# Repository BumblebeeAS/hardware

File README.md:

This repo contains Bumblebee's old firmware for the Electrical subteam. Most of the code is from before 2023 so please proceed with caution.

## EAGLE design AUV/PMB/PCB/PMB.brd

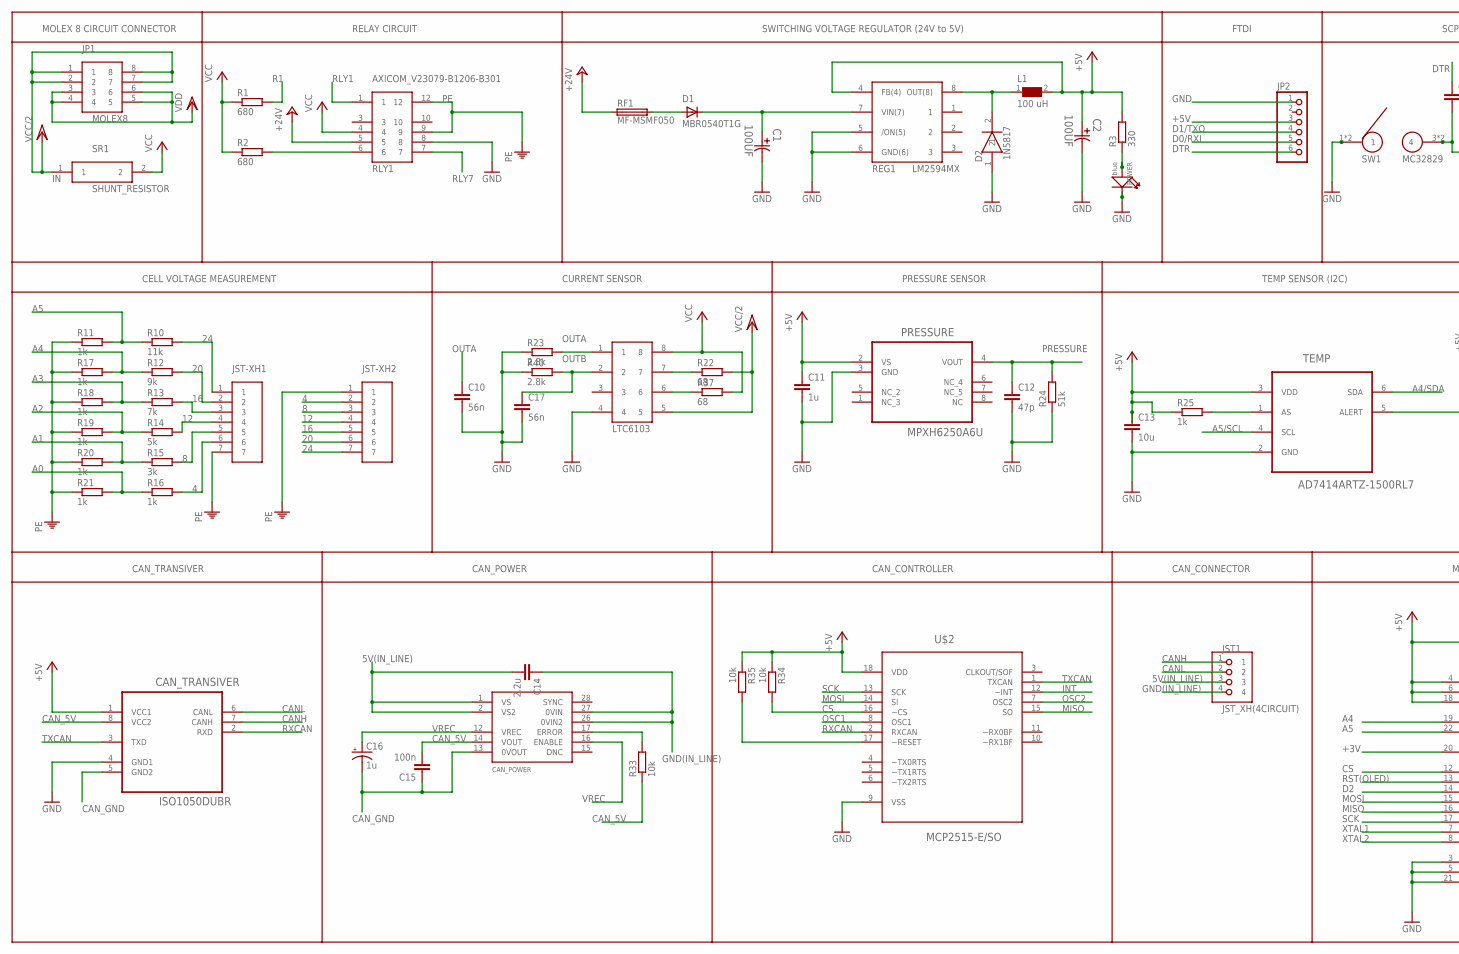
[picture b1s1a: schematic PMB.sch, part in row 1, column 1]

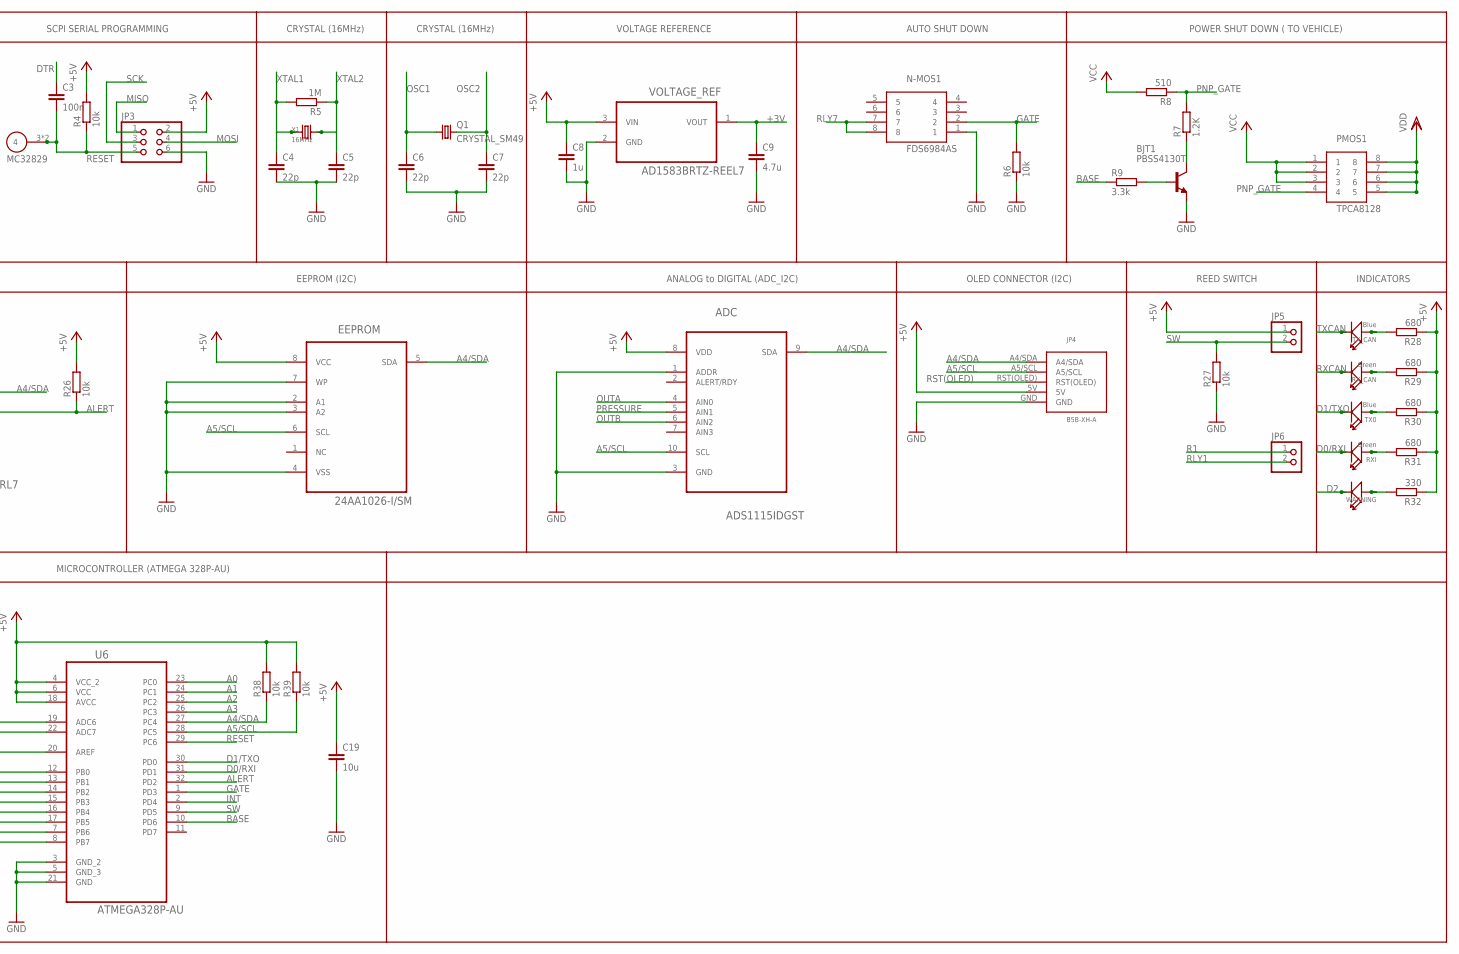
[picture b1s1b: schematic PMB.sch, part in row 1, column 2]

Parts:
ADC: ADS1115IDGST; SOP50P490X110-10N
BJT1: PBSS4130T; SOT-23
C1, C2: 100UF; CAPAE660X800N
C3, C15: 100n; 0805
C4, C5, C6, C7: 22p; 0805
C8, C11: 1u; 0805
C9: 4.7u; 0805
C10, C17: 56n; 0805
C12: 47p; 0805
C13, C19: 10u; 0805
C14: 2.2u; 0603-CAP
C16: 1u; EIA6032
CAN_POWER: DCR01SO; DCR01-SOIC28
CAN_TRANSIVER: ISO1050DUBR; SOIC254P1040X485-8N
D1: MBR0540T1G
D2: 1N5817
EEPROM: 24AA1026-I/SM; SOIC127P794X200-8N
JP1: MOLEX8; 026013144
JP2: PINHD-1X6/90; 1X06/90
JP3: PINHD-2X3; 2X03
JP4: B5B-XH-A
JP5, JP6: PINHD-1X2/90; 1X02/90
JST1: JST_XH(4CIRCUIT); JXT-XHP-4
JST-XH1, JST-XH2: JST_XH_1X7_2.5MM; SIL_1X8_2.5MM
L1: 100 uH; WE-PD_1030/1050
LTC1: LTC6103
N-MOS1: FDS6984AS; SO-8
PMOS1: TPCA8128
POWER: blue; LED-0805
PRESSURE: MPXH6250A6U; FREESCALE_CASE_1317
Q1: CRYSTAL_SM49; SM49
R1, R2, R28, R29, R30, R31: 680; R0805W
R3, R32: 330; R0805W
R4, R6, R26, R27, R33, R34, R35, R38, R39: 10k; R0805W
R5: 1M; R0805W
R7: 1.2K; R0805W
R8: 510; R0805W
R9: 3.3k; R0805W
R10: 11k; R0805W
R11, R16, R17, R18, R19, R20, R21, R25: 1k; R0805W
R12: 9k; R0805W
R13: 7k; R0805W
R14: 5k; R0805W
R15: 3k; R0805W
R22, R37: 68; R0805W
R23, R40: 2.8k; R0805W
R24: 51k; R0805W
REG1: LM2594MX
RF1: MF-MSMF050; MF-MSF050
RLY1: AXICOM_V23079-B1206-B301; RELAY_V23079_B1206
RXI: Green; LED-0805
RX_CAN: Green; LED-0805
SR1: SHUNT_RESISTOR; OARSXPR002FLF
SW1: MC32829
TEMP: AD7414ARTZ-1500RL7; SOT95P280X145-6N
TX0: Blue; LED-0805
TX_CAN: Blue; LED-0805
U6: ATMEGA328P-AU; QFP80P900X900X120-32N
U$2: MCP2515-E/SO; SOIC127P1030X265-18N
VOLTAGE_REF: AD1583BRTZ-REEL7; SOT95P237X112-3N
WARNING: LED-0805
X1: 16MHz; HC49US

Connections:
4: JST-XH1.6, JST-XH2.2, R16.2
5V(IN_LINE): C14.2, CAN_POWER.1 (VS), CAN_POWER.2 (VS2), JST1.3
8: JST-XH1.5, JST-XH2.3, R15.2
12: JST-XH1.4, JST-XH2.4, R14.2
16: JST-XH1.3, JST-XH2.5, R13.2
20: JST-XH1.2, JST-XH2.6, R12.2
24: JST-XH1.1, JST-XH2.7, R10.2
+3V: C9.1, U6.20 (AREF), VOLTAGE_REF.1 (VOUT)
+5V: ADC.8 (VDD), C2.1, C8.1, C11.1, C13.1, C19.1, CAN_TRANSIVER.1 (VCC1), EEPROM.8 (VCC), JP2.3, JP3.2, JP4.5V, JP5.1, L1.2, PRESSURE.2 (VS), R3.2, R4.2, R25.1, R26.2, R28.1, R29.1, R30.1, R31.1, R32.1, R34.1, R35.1, R38.2, R39.2, REG1.4 (FB(4)), TEMP.3 (VDD), U6.4 (VCC_2), U6.6 (VCC), U6.18 (AVCC), U$2.18 (VDD), VOLTAGE_REF.3 (VIN)
+24V: RF1.1, RLY1.5
A0: R16.1, R21.2, U6.23 (PC0)
A1: R15.1, R20.2, U6.24 (PC1)
A2: R14.1, R19.2, U6.25 (PC2)
A3: R13.1, R18.2, U6.26 (PC3)
A4: R12.1, R17.2, U6.19 (ADC6)
A4/SDA: ADC.9 (SDA), EEPROM.5 (SDA), JP4.A4/SDA, R38.1, TEMP.6 (SDA), U6.27 (PC4)
A5: R10.1, R11.2, U6.22 (ADC7)
A5/SCL: ADC.10 (SCL), EEPROM.6 (SCL), JP4.A5/SCL, R39.1, TEMP.4 (SCL), U6.28 (PC5)
ALERT: R26.1, TEMP.5 (ALERT), U6.32 (PD2)
BASE: R9.1, U6.10 (PD6)
CANH: CAN_TRANSIVER.7 (CANH), JST1.1
CANL: CAN_TRANSIVER.6 (CANL), JST1.2
CAN_5V: C15.2, CAN_POWER.14 (VOUT), CAN_TRANSIVER.8 (VCC2), R33.1
CAN_GND: C15.1, C16.P$2 (-), CAN_POWER.13 (0VOUT), CAN_TRANSIVER.5 (GND2)
CS: R34.2, U6.12 (PB0), U$2.16 (~CS)
D0/RXI: JP2.5, RXI.-, U6.31 (PD1)
D1/TXO: JP2.4, TX0.-, U6.30 (PD0)
D2: U6.14 (PB2), WARNING.-
DTR: C3.1, JP2.6
GATE: N-MOS1.2, R6.2, U6.1 (PD3)
GND: ADC.1 (ADDR), ADC.3 (GND), BJT1.E, C1.2, C2.2, C4.2, C5.2, C6.2, C7.2, C8.2, C9.2, C10.2, C11.2, C12.2, C13.2, C17.2, C19.2, CAN_TRANSIVER.4 (GND1), D2.1, EEPROM.2 (A1), EEPROM.3 (A2), EEPROM.4 (VSS), EEPROM.7 (WP), JP2.1, JP3.6, JP4.GND, LTC1.4, N-MOS1.1, POWER.-, PRESSURE.3 (GND), R6.1, R23.1, R24.1, R27.1, R40.1, REG1.5 (/ON(5)), REG1.6 (GND(6)), RLY1.8, SW1.1, SW1.2 (1), TEMP.2 (GND), U6.3 (GND_2), U6.5 (GND_3), U6.21 (GND), U$2.9 (VSS), VOLTAGE_REF.2 (GND)
GND(IN_LINE): C14.1, CAN_POWER.26 (0VIN2), CAN_POWER.27 (0VIN), JST1.4
INT: U6.2 (PD4), U$2.12 (~INT)
MISO: JP3.1, U6.16 (PB4), U$2.15 (SO)
MOSI: JP3.4, U6.15 (PB3), U$2.14 (SI)
unnamed: BJT1.B, R9.2
unnamed: D1.2, RF1.2
unnamed: C1.1, D1.1, REG1.7 (VIN(7))
unnamed: R2.2, RLY1.6
unnamed: D2.2, L1.1, REG1.8 (OUT(8))
unnamed: BJT1.C, R7.1
unnamed: POWER.+, R3.1
unnamed: LTC1.7, R22.1
unnamed: R25.2, TEMP.1 (AS)
unnamed: R32.2, WARNING.+
unnamed: R31.2, RXI.+
unnamed: R30.2, TX0.+
unnamed: R29.2, RX_CAN.+
unnamed: R28.2, TX_CAN.+
unnamed: LTC1.6, R37.1
unnamed: CAN_POWER.17 (ERROR), R33.2
unnamed: R35.2, U$2.17 (~RESET)
OSC1: C6.1, Q1.1, U$2.8 (OSC1)
OSC2: C7.1, Q1.2, U$2.7 (OSC2)
OUTA: ADC.4 (AIN0), C10.1, LTC1.1, R23.2
OUTB: ADC.6 (AIN2), C17.1, LTC1.2, R40.2
PE: JST-XH1.7, JST-XH2.1, R11.1, R17.1, R18.1, R19.1, R20.1, R21.1, RLY1.9, RLY1.12
PNP_GATE: PMOS1.4, R7.2, R8.1
PRESSURE: ADC.5 (AIN1), C12.1, PRESSURE.4 (VOUT), R24.2
R1: JP6.1, R1.2
RESET: C3.2, JP3.5, R4.1, SW1.3 (4), SW1.4, U6.29 (PC6)
RLY1: JP6.2, RLY1.1
RLY7: N-MOS1.7, N-MOS1.8, RLY1.7
RST(OLED): JP4.RST(OLED), U6.13 (PB1)
RXCAN: CAN_TRANSIVER.2 (RXD), RX_CAN.-, U$2.2 (RXCAN)
SCK: JP3.3, U6.17 (PB5), U$2.13 (SCK)
SW: JP5.2, R27.2, U6.9 (PD5)
TXCAN: CAN_TRANSIVER.3 (TXD), TX_CAN.-, U$2.1 (TXCAN)
VCC: LTC1.8, PMOS1.1, PMOS1.2, PMOS1.3, R1.1, R2.1, R8.2, R37.2, RLY1.4, SR1.2
VCC/2: JP1.1, JP1.2, JP1.7, JP1.8, LTC1.5, R22.2, SR1.1
VDD: JP1.3, JP1.4, JP1.5, JP1.6, PMOS1.5, PMOS1.6, PMOS1.7, PMOS1.8
VREC: C16.P$1 (+), CAN_POWER.12 (VREC), CAN_POWER.16 (ENABLE)
XTAL1: C4.1, R5.2, U6.7 (PB6), X1.1
XTAL2: C5.1, R5.1, U6.8 (PB7), X1.2

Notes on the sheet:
MOLEX 8 CIRCUIT CONNECTOR
RELAY CIRCUIT
SWITCHING VOLTAGE REGULATOR (24V to 5V)
FTDI
SCPI SERIAL PROGRAMMING
CRYSTAL (16MHz)
VOLTAGE REFERENCE
AUTO SHUT DOWN
POWER SHUT DOWN ( TO VEHICLE)
INDICATORS
REED SWITCH
OLED CONNECTOR (I2C)
ANALOG to DIGITAL (ADC_I2C)
EEPROM (I2C)
TEMP SENSOR (I2C)
PRESSURE SENSOR
CURRENT SENSOR
CELL VOLTAGE MEASUREMENT
CAN_TRANSIVER
CAN_POWER
CAN_CONTROLLER
CAN_CONNECTOR
MICROCONTROLLER (ATMEGA 328P-AU)

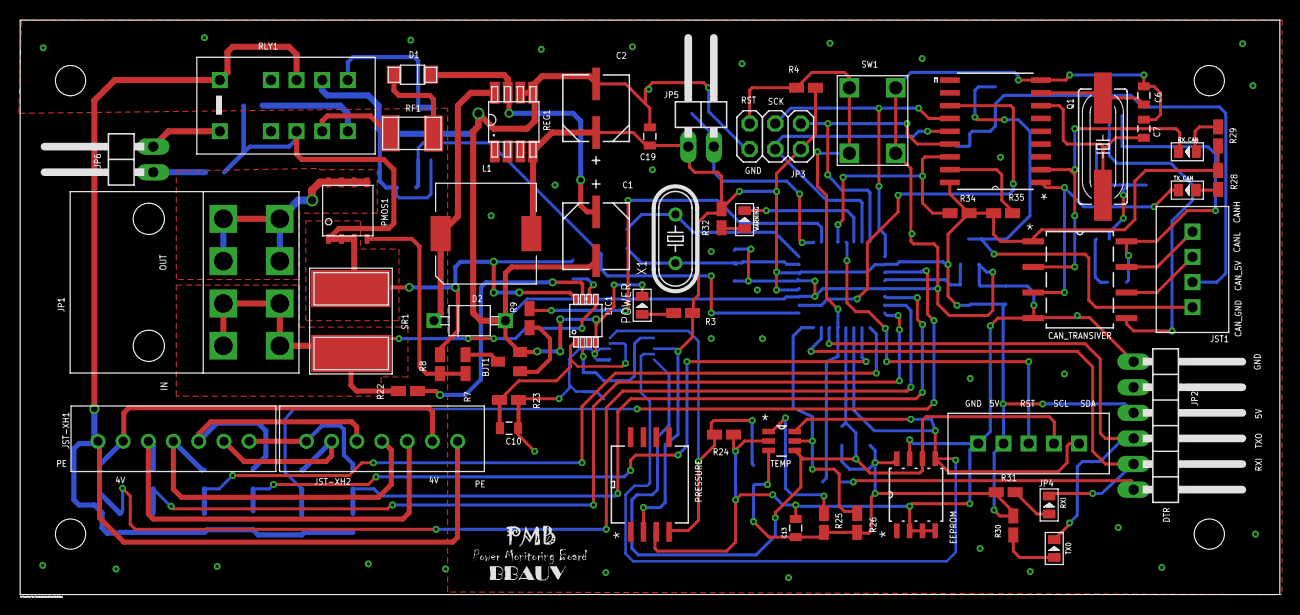
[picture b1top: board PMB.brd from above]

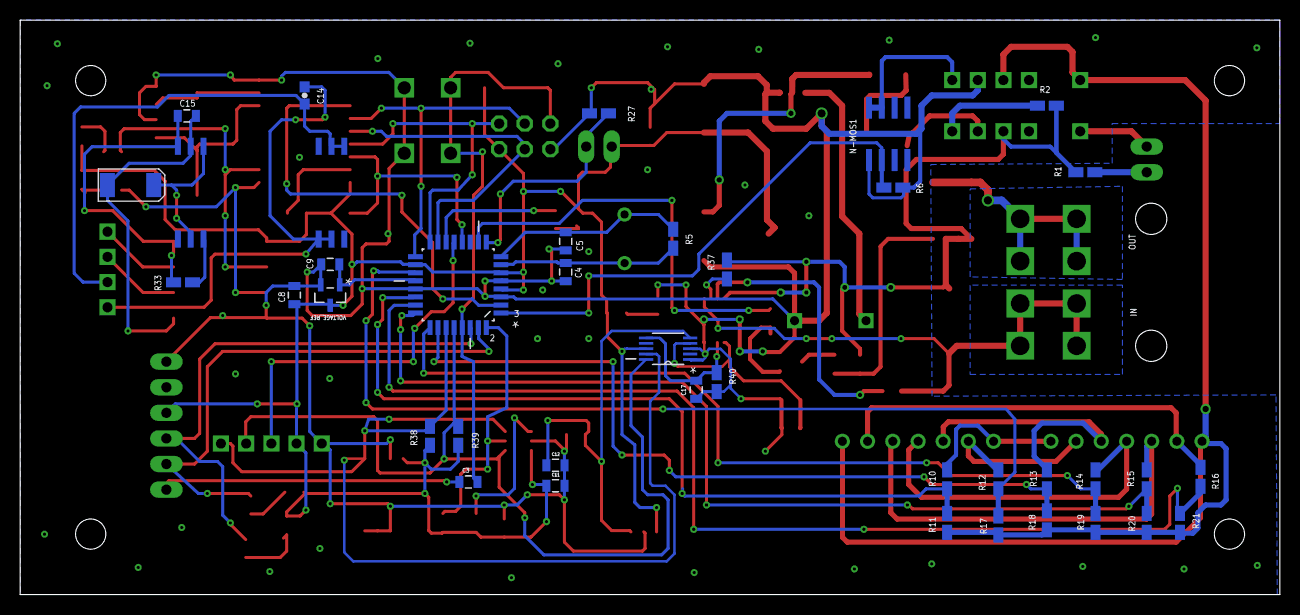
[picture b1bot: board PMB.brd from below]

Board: 2 copper layers, 125.0 x 57.0 mm, 95 parts (38 on the bottom side), 74 nets.

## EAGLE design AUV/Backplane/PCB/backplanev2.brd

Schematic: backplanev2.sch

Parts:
12VFAN: JP1E; JP1
24AA1026: 24AA1026-I/SM; SOIC127P794X200-8N
AD7414-1: AD7414-1; SOT23-6
ADUM1, ADUM2, ADUM3, ADUM4, ADUM1402: ADUM1402; SOIC127P1032X265-16N
C1, C2: 1uF; 1206
C3, C6, C7, C9, C12, C13, C24, C29, C32, C33, C35, C38, C39, C45, C51, C58, C59: 0.1uF; 0805
C4, C5, C8, C10, C11, C14, C25, C30, C31, C34, C36, C37, C40, C41, C44, C46, C47, C48, C52, C57, C60: 10uF; 0805
C15, C16, C17, C18, C22, C23, C42, C43: 22pF; 0805
C19, C20, C21, C26, C27, C28: 100nF; 0805
C53, C54: CAP_POL6032; EIA6032
C55, C56: CAP0603-CAP; 0603-CAP
D1, D3: 10V Zener; SOD-123
D2, D4: DIODESOD-123; SOD-123
FERRITE, FERRITE1, FERRITE2, FERRITE3, FERRITE4, FERRITE5, FERRITE6: FERRITE-74279201; RESC2013X65N
I2C: MA04-1
ISP: AVRISP-6; AVRISP
ISP-BP: AVRISP-6; AVRISP
JP5, JP6, JP8, JP9, JP10: JP2E; JP2
KILL-SWITCH: JP1E; JP1
LED1, LED2, LED3, LED4: LEDSMT1206; 1206
LED5: 5V logic power; 1206
LED-STRIP1, LED-STRIP2: LED STRIP; 1X04_LOCK
LTC4416: LTC4416; MSOP10
MCP2515-I/SO: MCP2515-I/SO; SOIC127P1034X264-18N
P-MOS, P-MOS1, P-MOS2, P-MOS3, P-MOS4, P-MOS5, P-MOS6: P-MOS; SOIC8
Q1, Q2, Q6: MMBT2222A; SOT23-3
Q3, Q4, Q5, Q7: 16Mhz; SM49
R1, R2: 10k; M0805
R3, R4, R7, R8, R33, R34, R35, R36, R39, R40, R41, R42, R51, R52, R53, R54, R57, R58, R59, R60, R61, R62, R63, R64, R65, R66, R67, R69, R70, R71, R75, R76, R77, R78, R93, R94, R95: 300; 0805
R5, R6, R9: 1M; 0805
R10, R11, R12, R13, R14, R15, R16, R17, R18, R31, R32, R37, R38, R44, R45, R49, R50, R55, R56, R68, R72, R74, R79, R101, R102, R103: RESISTOR0805-RES; 0805
R19, R20, R21, R22, R23, R24, R25, R26, R81, R82, R83, R84, R85, R86, R87, R88, R89, R90, R91, R92: R-EU_M0805; M0805
R27, R29, R43, R46, R47, R48, R73: 10k; 0805
R28, R30, R80: 1k; 0805
R104, R105: 120; 0805
RX: LEDCHIPLED_0805; CHIPLED_0805
RX-BP: LEDCHIPLED_0805; CHIPLED_0805
RX-CAN: LEDCHIPLED_0805; CHIPLED_0805
RX-PMB1, RX-PMB2: LEDCHIPLED_0805; CHIPLED_0805
RX-SA: LEDCHIPLED_0805; CHIPLED_0805
RX-TE: LEDCHIPLED_0805; CHIPLED_0805
RX-TH: LEDCHIPLED_0805; CHIPLED_0805
RXCAN: LEDCHIPLED_0805; CHIPLED_0805
SA: LEDCHIPLED_0805; CHIPLED_0805
SPARE: SA SPARE; 2X05
SPARE2: SA SPARE; 1X02
SW1, SW2: RESET; MC32829
SW_5V_BP, SW_5V_CAN, SW_5V_SA, SW_5V_TE, SW_5V_TH: LEDCHIPLED_0805; CHIPLED_0805
SW_USB_BP: LEDCHIPLED_0805; CHIPLED_0805
SW_USB_CAN: LEDCHIPLED_0805; CHIPLED_0805
SW_USB_PMB1, SW_USB_PMB2: LEDCHIPLED_0805; CHIPLED_0805
SW_USB_SA, SW_USB_SA1: LEDCHIPLED_0805; CHIPLED_0805
SW_USB_TE: LEDCHIPLED_0805; CHIPLED_0805
TE: LEDCHIPLED_0805; CHIPLED_0805
TH: LEDCHIPLED_0805; CHIPLED_0805
TX: LEDCHIPLED_0805; CHIPLED_0805
TX-BP: LEDCHIPLED_0805; CHIPLED_0805
TX-CAN: LEDCHIPLED_0805; CHIPLED_0805
TX-PMB1, TX-PMB2: LEDCHIPLED_0805; CHIPLED_0805
TX-SA: LEDCHIPLED_0805; CHIPLED_0805
TX-TE: LEDCHIPLED_0805; CHIPLED_0805
TX-TH: LEDCHIPLED_0805; CHIPLED_0805
TXCAN: LEDCHIPLED_0805; CHIPLED_0805
U1: ATMEGA328P_TQFP; TQFP32-08
U2, U3, U6, U7, U8, U9, U11: FT232RLSSOP; SSOP28DB
U4, U5: DCR010505U; SOIC127P1032X265-12NA
U13: ATMEGA2560-16AU; QFP50P1600X1600X120-100N
U$1: TERM-BLOCK-4POS
U$2, U$50, U$70: PLATED-HOLE
U$3, U$26, U$27: RJ45-DUAL-SOCKET; RJ45DOUBLESOCKET
U$4: MINIFIT-16CKT-STRAIGHTHEADER
U$5, U$22: 100UF; 100UF-AFK-CAP
U$6, U$12, U$55, U$56, U$60: LTC6103; MSOP8
U$7, U$32: IRLR3636PBF(N-MOS); TO252
U$8, U$9, U$10, U$17, U$19: S6B-XH-SM4-TB(LF)(SN)
U$11, U$16: FCN-365P040-BACKPLANE; FCN-365J040-BACKPLANE-JACK
U$13: MICROFIT-2CK-HEADER; MICROFIT-2CKT-HEADER
U$14: MICROFIT-8CKT-HEADER
U$15: MICROFIT-10CKT-HEADER
U$18, U$57: ADS1115; SOP50P490X110-10N
U$20, U$21, U$58, U$59, U$63: LVK25R002FER(CURRENT-SENSE-R)
U$23, U$24, U$28, U$31, U$33, U$44, U$46, U$48, U$49, U$51, U$53, U$54: MIC2005A-1YM5; SOT23-5
U$25: MCP2515-I/SO; SOIC127P1034X264-18N
U$29, U$30, U$41, U$47: USB-DUAL-SOCKET
U$34, U$40: ISO1050; DUB-8
U$35, U$36, U$37, U$38: MINIFIT-4CKT-2ROW-W2B-90DEG
U$39: MOLEX-MINIFIT-10CKT2ROW-90DEG-HEADER
U$45: MINIFIT-10CKT-STRAIGHTHEADER
U$52, U$61, U$64, U$65: MICROFIT-4CKT-HEADER
U$62: ADS1115DGST; SOP50P490X110-10N
U$76, U$78: N-MOS-SOIC8; SOIC8
U$77: N-MOS; SOIC8

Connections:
3.3V: U$11.B19, U$39.A5, U$39.B5
5V: 24AA1026.8 (VCC), AD7414-1.3 (VDD), C20.1, C21.1, C27.1, C28.1, C47.1, C55.1, C56.1, I2C.4, LED5.A, MCP2515-I/SO.18 (VDD), P-MOS1.1 (S), P-MOS1.2 (S), P-MOS1.3 (S), P-MOS5.1 (S), P-MOS5.2 (S), P-MOS5.3 (S), P-MOS6.1 (S), P-MOS6.2 (S), P-MOS6.3 (S), R17.2, R27.2, R29.2, R43.2, R46.2, R48.1, R72.1, R73.2, R79.2, R103.1, U1.4 (VCC), U1.6 (VCC), U4.1 (VS_2), U4.2 (VS), U5.1 (VS_2), U5.2 (VS), U13.10 (VCC_3), U13.31 (VCC_2), U13.61 (VCC_4), U13.80 (VCC), U13.100 (AVCC), U$1.P$3, U$5.POS (+), U$10.P$6, U$17.P$6, U$18.8 (VDD), U$19.P$6, U$22.POS (+), U$24.1 (VIN), U$24.3 (EN), U$25.18 (VDD), U$34.1 (VCC1), U$39.A3, U$39.B3, U$40.1 (VCC1), U$54.1 (VIN), U$54.3 (EN), U$57.8 (VDD), U$62.1 (ADDR), U$62.8 (VDD)
5VSA: P-MOS1.5 (D), P-MOS1.6 (D), P-MOS1.7 (D), P-MOS1.8 (D), R68.1, U$16.B19, U$46.1 (VIN), U$46.3 (EN)
5VTE: P-MOS6.5 (D), P-MOS6.6 (D), P-MOS6.7 (D), P-MOS6.8 (D), R66.1, U$11.B20, U$48.1 (VIN), U$48.3 (EN)
5VTH: P-MOS5.5 (D), P-MOS5.6 (D), P-MOS5.7 (D), P-MOS5.8 (D), R67.1, U$33.1 (VIN), U$33.3 (EN), U$45.L2
5V_ADC: R17.1, R18.2, U13.93 (PF4_(ADC4/TCK))
5V_CAN_BP: C19.2, C54.P$1 (+), R44.1, U5.14 (VO), U$40.8 (VCC2)
5V_UART_CAN: C26.2, C53.P$1 (+), R47.1, U4.14 (VO), U$34.8 (VCC2)
12IDSFI1: JP5.1, JP8.1, JP10.3, KILL-SWITCH.2, Q2.2 (E)
12V: 12VFAN.1, LED-STRIP1.1, LED-STRIP2.1, R15.2, U$1.P$2, U$13.PIN1, U$39.A2, U$39.B2
12V-TO-M4: U$39.A4, U$39.B4, U$64.BOT1 (B1), U$64.TOP1
12V_ADC: R15.1, R16.2, U13.92 (PF5_(ADC5/TMS))
24V1: LTC4416.8 (VS), P-MOS.1 (S), P-MOS.2 (S), P-MOS.3 (S), P-MOS3.1 (S), P-MOS3.2 (S), P-MOS3.3 (S), R101.2, U$20.I2
24V1_ADC: R101.1, R102.2, U13.94 (PF3_(ADC3))
24V2: U$20.I1, U$21.I2, U$52.BOT1 (B1), U$52.TOP1, U$61.BOT1 (B1), U$61.TOP1
24V2SA: U$14.BOT1 (B1), U$14.BOT2 (B2), U$14.BOT3 (B3), U$14.BOT4 (B4), U$15.T5, U$16.B20, U$21.I1
24V-ACOU: U$3.U4, U$3.U5, U$58.I1
24V-NAV: U$27.U4, U$27.U5, U$63.I1
24V-POE: U$1.P$4, U$58.I2, U$59.I2, U$63.I2, U$65.BOT1 (B1), U$65.TOP1
24V-SONAR: U$26.U4, U$26.U5, U$59.I1
A+: U$26.L1, U$26.U1
A-: U$26.L2, U$26.U2
ACOU-A+: U$3.L1, U$3.U1
ACOU-A-: U$3.L2, U$3.U2
ACOU-B+: U$3.L3, U$3.U3
ACOU-B-: U$3.L6, U$3.U6
ACOU_EN: U13.51 (PG0_(~WR)), U$77.4 (G)
ACOU_GND: U$3.U7, U$3.U8, U$77.5 (D), U$77.6 (D), U$77.7 (D), U$77.8 (D)
B1: LED-STRIP2.2, U$16.B16
B2: LED-STRIP1.2, U$16.A16
B+: U$26.L3, U$26.U3
B-: U$26.L6, U$26.U6
BATT1: LED1.A, LED2.C, LTC4416.9 (V1), P-MOS4.1 (S), P-MOS4.2 (S), P-MOS4.3 (S), R1.2, R6.2, R11.2, U$4.L5, U$4.L6, U$4.U5, U$4.U6, U$37.LL, U$37.LR, U$37.UL, U$37.UR
BATT1_ADC: R11.1, R12.2, U13.95 (PF2_(ADC2))
BATT2: LED3.A, LED4.C, LTC4416.7 (V2), P-MOS2.1 (S), P-MOS2.2 (S), P-MOS2.3 (S), R10.2, R13.2, U$4.L7, U$4.L8, U$4.U7, U$4.U8, U$38.LL, U$38.LR, U$38.UL, U$38.UR
BATT2_ADC: R13.1, R14.2, U13.96 (PF1_(ADC1))
CANH: R104.2, R105.2, U$10.P$4, U$11.A1, U$16.A1, U$17.P$4, U$19.P$4, U$34.7 (CANH), U$40.7 (CANH), U$45.L1
CANL: R104.1, R105.1, U$10.P$3, U$11.A2, U$16.A2, U$17.P$3, U$19.P$3, U$34.6 (CANL), U$40.6 (CANL), U$45.U1
CAN_RXD: RXCAN.A, U$25.2 (RXCAN), U$34.2 (RXD)
CAN_RXD_BP: MCP2515-I/SO.2 (RXCAN), RX.A, U$40.2 (RXD)
CAN_TXD_BP: MCP2515-I/SO.1 (TXCAN), TX.A, U$40.3 (TXD)
CTS_BP: ADUM1402.11 (VID)
CTS_CAN: ADUM1.11 (VID)
CTS_CAN_ISO: ADUM1.6 (VOD)
CTS_TH_ISO: ADUM2.6 (VOD)
D+_BP: U2.15 (USBDP), U$30.U3 (UDP)
D+_CAN: U6.15 (USBDP), U$41.U3 (UDP)
D+_PMB1: U9.15 (USBDP), U$29.L3 (LDP)
D+_PMB2: U11.15 (USBDP), U$29.U3 (UDP)
D+_SA: U7.15 (USBDP), U$47.L3 (LDP)
D+_TE: U8.15 (USBDP), U$47.U3 (UDP)
D+_TH: U3.15 (USBDP), U$30.L3 (LDP)
D-_BP: U2.16 (USBDM), U$30.U2 (UDM)
D-_CAN: U6.16 (USBDM), U$41.U2 (UDM)
D-_PMB1: U9.16 (USBDM), U$29.L2 (LDM)
D-_PMB2: U11.16 (USBDM), U$29.U2 (UDM)
D-_SA: U7.16 (USBDM), U$47.L2 (LDM)
D-_TE: U8.16 (USBDM), U$47.U2 (UDM)
D-_TH: U3.16 (USBDM), U$30.L2 (LDM)
DTR_BP: ADUM1402.13 (VOB), C44.1
DTR_BP_ISO: ADUM1402.4 (VIB), U2.2 (DTR)
DTR_CAN: ADUM1.13 (VOB), C41.1
DTR_CAN_ISO: ADUM1.4 (VIB), U6.2 (DTR)
DTR_PMB1_ISO: U9.2 (DTR), U$8.P$6
DTR_PMB2_ISO: U11.2 (DTR), U$9.P$6
DTR_SA: ADUM3.13 (VOB), U$16.B2
DTR_SA_ISO: ADUM3.4 (VIB), U7.2 (DTR)
DTR_TE: ADUM4.13 (VOB), U$11.B2
DTR_TE_ISO: ADUM4.4 (VIB), U8.2 (DTR)
DTR_TH: ADUM2.13 (VOB), U$45.L3
DTR_TH_ISO: ADUM2.4 (VIB), U3.2 (DTR)
G1: LED-STRIP2.3, U$16.B17
G2: LED-STRIP1.3, U$16.A17
GATE1: LTC4416.10 (G1), P-MOS3.4 (G), P-MOS4.4 (G)
GATE2: LTC4416.6 (G2), P-MOS.4 (G), P-MOS2.4 (G)
GND: 12VFAN.2, 24AA1026.2 (A1), 24AA1026.3 (A2), 24AA1026.4 (VSS), 24AA1026.7 (WP), AD7414-1.1 (AS), AD7414-1.2 (GND), ADUM1.9 (GND2_2), ADUM1.15 (GND2), ADUM2.9 (GND2_2), ADUM2.15 (GND2), ADUM3.9 (GND2_2), ADUM3.15 (GND2), ADUM4.9 (GND2_2), ADUM4.15 (GND2), ADUM1402.9 (GND2_2), ADUM1402.15 (GND2), C4.2, C6.2, C10.2, C12.2, C15.1, C16.1, C17.1, C18.1, C19.1, C20.2, C21.2, C22.1, C23.1, C25.2, C26.1, C27.2, C28.2, C30.2, C32.2, C36.2, C38.2, C42.1, C43.1, C47.2, C48.1, C55.2, C56.2, C58.2, I2C.1, ISP.6 (GND), ISP-BP.6 (GND), JP8.3, JP10.1, KILL-SWITCH.1, LTC4416.3 (GND), MCP2515-I/SO.9 (VSS), R2.1, R12.1, R14.1, R16.1, R18.1, R19.2, R20.2, R23.2, R24.2, R36.2, R42.2, R54.2, R60.2, R61.1, R62.1, R78.2, R81.2, R82.2, R85.2, R86.2, R89.2, R90.2, R93.1, R94.1, R95.1, R102.1, SA.C, SW1.P$1, SW1.P$4, SW2.P$1, SW2.P$4, TE.C, TH.C, U1.3 (GND), U1.21 (AGND), U4.13 (0VOUT), U4.26 (0VIN_2), U4.27 (0VIN), U5.13 (0VOUT), U5.26 (0VIN_2), U5.27 (0VIN), U13.11 (GND_2), U13.32 (GND_4), U13.62 (GND_3), U13.81 (GND_5), U13.99 (GND), U$1.P$1, U$2.P$1, U$4.L1, U$4.L2, U$4.L3, U$4.L4, U$4.U1, U$4.U2, U$4.U3, U$4.U4, U$5.NEG (-), U$6.4 (V-), U$7.3 (D), U$10.P$1, U$11.A19, U$11.A20, U$11.B1, U$12.4 (V-), U$14.TOP3, U$14.TOP4, U$16.A19, U$16.A20, U$16.B1, U$17.P$1, U$18.3 (GND), U$19.P$1, U$22.NEG (-), U$24.2 (GND), U$25.9 (VSS), U$32.3 (D), U$33.2 (GND), U$34.4 (GND1), U$34.5 (GND2), U$39.A1, U$39.B1, U$40.4 (GND1), U$40.5 (GND2), U$45.U2, U$46.2 (GND), U$48.2 (GND), U$52.BOT2 (B2), U$52.TOP2, U$54.2 (GND), U$55.4 (V-), U$56.4 (V-), U$57.3 (GND), U$60.4 (V-), U$61.BOT2 (B2), U$61.TOP2, U$62.3 (GND), U$64.BOT2 (B2), U$64.TOP2, U$65.BOT2 (B2), U$65.TOP2, U$70.P$1, U$76.1 (S), U$76.2 (S), U$76.3 (S), U$77.1 (S), U$77.2 (S), U$77.3 (S), U$78.1 (S), U$78.2 (S), U$78.3 (S)
GND_IN: C1.2, C2.2, D1.A, D3.A, R3.1, R4.1, R5.1, R7.1, R8.1, R9.1, U$7.2 (S), U$32.2 (S), U$35.LL, U$35.LR, U$35.UL, U$35.UR, U$36.LL, U$36.LR, U$36.UL, U$36.UR
INTERRUPT_UART_CAN: U$25.12 (~INT)
INT_BP: MCP2515-I/SO.12 (~INT)
L1: U$14.TOP1, U$16.B15
L2: U$14.TOP2, U$16.A15
LVE1: ADUM1402.7 (VE1), R32.1
LVE2: ADUM2.7 (VE1), R38.1
LVE3: ADUM3.7 (VE1), R50.1
LVE4: ADUM4.7 (VE1), R56.1
LVE7: ADUM1.7 (VE1), R74.1
M1: U$15.B5, U$16.B14
M2: U$15.B4, U$16.A14
M3: U$15.T4, U$16.B13
M4: U$15.B3, U$16.A13
M5: U$15.T3, U$16.B12
M6: U$15.B2, U$16.A12
M7: U$15.T2, U$16.B11
M8: U$15.B1, U$16.A11
M9: U$15.T1, U$16.B10
MISO_BP: ISP-BP.1 (MISO), MCP2515-I/SO.15 (SO), U13.22 ((MISO/PCINT3)_PB3)
MISO_UART_CAN: ISP.1 (MISO), U1.16 (PB4(MISO)), U$25.15 (SO)
MOSI_BP: ISP-BP.4 (MOSI), MCP2515-I/SO.14 (SI), U13.21 ((MOSI/PCINT2)_PB2)
MOSI_UART_CAN: ISP.4 (MOSI), U1.15 (PB3(MOSI/OC2)), U$25.14 (SI)
unnamed: P-MOS3.5 (D), P-MOS3.6 (D), P-MOS3.7 (D), P-MOS3.8 (D), P-MOS4.5 (D), P-MOS4.6 (D), P-MOS4.7 (D), P-MOS4.8 (D)
unnamed: P-MOS.5 (D), P-MOS.6 (D), P-MOS.7 (D), P-MOS.8 (D), P-MOS2.5 (D), P-MOS2.6 (D), P-MOS2.7 (D), P-MOS2.8 (D)
unnamed: R33.2, TX-BP.C
unnamed: R33.1, U2.23 (TXLED)
unnamed: R34.2, RX-BP.C
unnamed: FERRITE.2, U$23.1 (VIN), U$23.3 (EN)
unnamed: ADUM1402.10 (VE2), R31.1
unnamed: R35.2, SW_USB_BP.C
unnamed: R36.1, SW_5V_BP.A
unnamed: R39.2, RX-TH.C
unnamed: R34.1, U2.22 (RXLED)
unnamed: R40.2, TX-TH.C
unnamed: ADUM2.10 (VE2), R37.1
unnamed: FERRITE1.2, U$31.1 (VIN), U$31.3 (EN)
unnamed: R41.2, SW_USB_SA.C
unnamed: R39.1, U3.22 (RXLED)
unnamed: R40.1, U3.23 (TXLED)
unnamed: R42.1, SW_5V_TH.A
unnamed: C22.2, Q3.1, U$25.7 (OSC2)
unnamed: C23.2, Q3.2, U$25.8 (OSC1)
unnamed: C15.2, MCP2515-I/SO.7 (OSC2), Q4.1
unnamed: C16.2, MCP2515-I/SO.8 (OSC1), Q4.2
unnamed: R46.1, U$25.17 (~RESET)
unnamed: C42.2, Q7.1, U1.7 (PB6(XTAL1/TOSC1))
unnamed: MCP2515-I/SO.17 (~RESET), R43.1
unnamed: R47.2, U4.17 (~ERROR)
unnamed: R51.2, TX-SA.C
unnamed: R52.2, RX-SA.C
unnamed: ADUM3.10 (VE2), R49.1
unnamed: FERRITE2.2, U$44.1 (VIN), U$44.3 (EN)
unnamed: R53.2, SW_USB_SA1.C
unnamed: R51.1, U7.23 (TXLED)
unnamed: R52.1, U7.22 (RXLED)
unnamed: LED2.A, R3.2
unnamed: LED1.C, R4.2
unnamed: R54.1, SW_5V_SA.A
unnamed: R57.2, TX-TE.C
unnamed: R58.2, RX-TE.C
unnamed: ADUM4.10 (VE2), R55.1
unnamed: FERRITE3.2, U$28.1 (VIN), U$28.3 (EN)
unnamed: R59.2, SW_USB_TE.C
unnamed: R61.2, TXCAN.C
unnamed: R62.2, RXCAN.C
unnamed: R93.2, TX.C
unnamed: R63.2, TX-PMB1.C
unnamed: R64.2, RX-PMB1.C
unnamed: R66.2, TE.A
unnamed: FERRITE4.2, U$49.1 (VIN), U$49.3 (EN)
unnamed: R75.2, RX-CAN.C
unnamed: R76.2, TX-CAN.C
unnamed: R67.2, TH.A
unnamed: R57.1, U8.23 (TXLED)
unnamed: R58.1, U8.22 (RXLED)
unnamed: R60.1, SW_5V_TE.A
unnamed: JP5.2, P-MOS5.4 (G), R29.1
unnamed: JP5.3, Q2.3 (C)
unnamed: JP6.2, P-MOS1.4 (G), R27.1
unnamed: Q2.1 (B), R30.1
unnamed: JP6.3, Q1.3 (C)
unnamed: Q1.1 (B), R28.1
unnamed: JP6.1, JP8.2, Q1.2 (E)
unnamed: ADUM1.10 (VE2), R45.1
unnamed: R65.2, SW_USB_PMB1.C
unnamed: R63.1, U9.23 (TXLED)
unnamed: R64.1, U9.22 (RXLED)
unnamed: R68.2, SA.A
unnamed: R69.2, TX-PMB2.C
unnamed: R70.2, RX-PMB2.C
unnamed: R44.2, U5.17 (~ERROR)
unnamed: R75.1, U6.22 (RXLED)
unnamed: FERRITE5.2, U$51.1 (VIN), U$51.3 (EN)
unnamed: R71.2, SW_USB_PMB2.C
unnamed: R69.1, U11.23 (TXLED)
unnamed: R70.1, U11.22 (RXLED)
unnamed: R76.1, U6.23 (TXLED)
unnamed: R94.2, RX.C
unnamed: LED5.C, R95.2
unnamed: LTC4416.2 (E1), R1.1
unnamed: LTC4416.4 (!E2), R2.2
unnamed: C48.2, U13.98 (AREF)
unnamed: C43.2, Q7.2, U1.8 (PB7(XTAL2/TOSC2))
unnamed: C17.2, Q5.1, U13.33 (XTAL2)
unnamed: C18.2, Q5.2, U13.34 (XTAL1)
unnamed: FERRITE6.2, U$53.1 (VIN), U$53.3 (EN)
unnamed: R77.2, SW_USB_CAN.C
unnamed: R78.1, SW_5V_CAN.A
unnamed: Q6.1 (B), R80.1
unnamed: JP9.3, Q6.3 (C)
unnamed: JP9.2, P-MOS6.4 (G), R79.1
unnamed: JP9.1, JP10.2, Q6.2 (E)
unnamed: R83.1, U$55.5 (+INB), U$58.V1
unnamed: R84.1, U$55.8 (+INA), U$58.V2
unnamed: R81.1, U$55.1 (OUTA), U$57.4 (AIN0)
unnamed: R82.1, U$55.2 (OUTB), U$57.5 (AIN1)
unnamed: R83.2, U$55.7 (-INA)
unnamed: R84.2, U$55.6 (-INB)
unnamed: R87.1, U$56.5 (+INB), U$59.V1
unnamed: R88.1, U$56.8 (+INA), U$59.V2
unnamed: R85.1, U$56.1 (OUTA), U$57.7 (AIN3)
unnamed: R86.1, U$56.2 (OUTB), U$57.6 (AIN2)
unnamed: R87.2, U$56.7 (-INA)
unnamed: R88.2, U$56.6 (-INB)
unnamed: R91.1, U$60.5 (+INB), U$63.V1
unnamed: R92.1, U$60.8 (+INA), U$63.V2
unnamed: R89.1, U$60.1 (OUTA), U$62.4 (AIN0)
unnamed: R90.1, U$60.2 (OUTB), U$62.5 (AIN1)
unnamed: R91.2, U$60.7 (-INA)
unnamed: R92.2, U$60.6 (-INB)
unnamed: C1.1, D2.A, R5.2, R6.1, U$32.1 (G)
unnamed: LED4.A, R7.2
unnamed: D1.C, D2.C
unnamed: LED3.C, R8.2
unnamed: C2.1, D4.A, R9.2, R10.1, U$7.1 (G)
unnamed: D3.C, D4.C
unnamed: R21.1, U$6.5 (+INB), U$20.V1
unnamed: R22.1, U$6.8 (+INA), U$20.V2
unnamed: R19.1, U$6.1 (OUTA), U$18.7 (AIN3)
unnamed: R20.1, U$6.2 (OUTB), U$18.6 (AIN2)
unnamed: R21.2, U$6.7 (-INA)
unnamed: R22.2, U$6.6 (-INB)
unnamed: R25.1, U$12.5 (+INB), U$21.V1
unnamed: R26.1, U$12.8 (+INA), U$21.V2
unnamed: R23.1, U$12.1 (OUTA), U$18.4 (AIN0)
unnamed: R24.1, U$12.2 (OUTB), U$18.5 (AIN1)
unnamed: R25.2, U$12.7 (-INA)
unnamed: R26.2, U$12.6 (-INB)
NAV-A+: U$27.L1, U$27.U1
NAV-A-: U$27.L2, U$27.U2
NAV-B+: U$27.L3, U$27.U3
NAV-B-: U$27.L6, U$27.U6
NAV_EN: U13.53 (PC0_(A8)), U$76.4 (G)
NAV_GND: U$27.U7, U$27.U8, U$76.5 (D), U$76.6 (D), U$76.7 (D), U$76.8 (D)
PRES: U$13.PIN2, U$16.A10
R1: LED-STRIP2.4, U$16.B18
R2: LED-STRIP1.4, U$16.A18
RESET_BP: C44.2, ISP-BP.5 (RST), R103.2, SW2.P$2, SW2.P$3, U13.30 (~RESET)
RESET_UART_CAN: C41.2, ISP.5 (RST), R72.2, SW1.P$2, SW1.P$3, U1.29 (PC6(/RESET))
RX_BP: ADUM1402.14 (VOA), U13.2 ((RXD0/PCINT8)_PE0)
RX_BP_ISO: ADUM1402.3 (VIA), U2.1 (TXD)
RX_CAN: ADUM1.14 (VOA), TXCAN.A, U1.30 (PD0(RXD)), U$25.1 (TXCAN), U$34.3 (TXD)
RX_CAN_ISO: ADUM1.3 (VIA), U6.1 (TXD)
RX_PMB1_ISO: U9.1 (TXD), U$8.P$4
RX_PMB2_ISO: U11.1 (TXD), U$9.P$4
RX_SA: ADUM3.14 (VOA), U$16.B3
RX_SA_1: SPARE2.2, U$16.A3
RX_SA_ISO: ADUM3.3 (VIA), U7.1 (TXD)
RX_TE: ADUM4.14 (VOA), U$11.B3
RX_TE_ISO: ADUM4.3 (VIA), U8.1 (TXD)
RX_TH: ADUM2.14 (VOA), U$45.U4
RX_TH_ISO: ADUM2.3 (VIA), U3.1 (TXD)
SA_EN: R28.2, U13.50 ((T0)_PD7)
SCK_BP: ISP-BP.3 (SCK), MCP2515-I/SO.13 (SCK), U13.20 ((SCK/PCINT1)_PB1)
SCK_UART_CAN: ISP.3 (SCK), U1.17 (PB5(SCK)), U$25.13 (SCK)
SCL: 24AA1026.6 (SCL), AD7414-1.4 (SCL), I2C.2, U13.43 ((SCL/INT0)_PD0), U$18.1 (ADDR), U$18.10 (SCL), U$57.10 (SCL), U$62.10 (SCL)
SDA: 24AA1026.5 (SDA), AD7414-1.6 (SDA), I2C.3, U13.44 ((SDA/INT1)_PD1), U$18.9 (SDA), U$57.1 (ADDR), U$57.9 (SDA), U$62.9 (SDA)
SONAR_EN: U13.52 (PG1_(~RD)), U$78.4 (G)
SONAR_GND: U$26.U7, U$26.U8, U$78.5 (D), U$78.6 (D), U$78.7 (D), U$78.8 (D)
SPARE1: SPARE.2, U$16.B9
SPARE2: SPARE.4, U$16.B8
SPARE3: SPARE.6, U$16.B7
SPARE4: SPARE.8, U$16.B6
SPARE5: SPARE.10, U$16.B5
SPARE6: SPARE.1, U$16.A9
SPARE7: SPARE.3, U$16.A8
SPARE8: SPARE.5, U$16.A7
SPARE9: SPARE.7, U$16.A6
SPARE10: SPARE.9, U$16.A5
SPARE_TH_1: U$45.U3
SPARE_TH_2: U$45.U5
SPARE_TH_3: U$45.L5
SS_BP: MCP2515-I/SO.16 (~CS), R73.1, U13.17 ((OC4C)_PH5)
SS_UART_CAN: R48.2, U1.12 (PB0(ICP)), U$25.16 (~CS)
SW_5V_BP: ADUM1402.16 (VDD2), C4.1, C6.1, R31.2, SW_5V_BP.C, U$24.5 (VOUT)
SW_5V_CAN: ADUM1.16 (VDD2), C25.1, C58.1, R45.2, SW_5V_CAN.C, U$54.5 (VOUT)
SW_5V_SA: ADUM3.16 (VDD2), C30.1, C32.1, R49.2, SW_5V_SA.C, U$46.5 (VOUT)
SW_5V_TE: ADUM4.16 (VDD2), C36.1, C38.1, R55.2, SW_5V_TE.C, U$48.5 (VOUT)
SW_5V_TH: ADUM2.16 (VDD2), C10.1, C12.1, R37.2, SW_5V_TH.C, U$33.5 (VOUT)
SW_USB+_BP: ADUM1402.1 (VDD1), C3.1, C5.1, C7.1, C8.1, R32.2, R35.1, RX-BP.A, TX-BP.A, U2.4 (VCCIO), U2.20 (VCC), U$23.5 (VOUT)
SW_USB+_CAN: ADUM1.1 (VDD1), C24.1, C57.1, C59.1, C60.1, R74.2, R77.1, RX-CAN.A, TX-CAN.A, U6.4 (VCCIO), U6.20 (VCC), U$53.5 (VOUT)
SW_USB+_PMB1: C45.1, C46.1, R65.1, RX-PMB1.A, TX-PMB1.A, U9.4 (VCCIO), U9.20 (VCC), U$8.P$3, U$49.5 (VOUT)
SW_USB+_PMB2: C51.1, C52.1, R71.1, RX-PMB2.A, TX-PMB2.A, U11.4 (VCCIO), U11.20 (VCC), U$9.P$3, U$51.5 (VOUT)
SW_USB+_SA: ADUM3.1 (VDD1), C29.1, C31.1, C33.1, C34.1, R50.2, R53.1, RX-SA.A, TX-SA.A, U7.4 (VCCIO), U7.20 (VCC), U$44.5 (VOUT)
SW_USB+_TE: ADUM4.1 (VDD1), C35.1, C37.1, C39.1, C40.1, R56.2, R59.1, RX-TE.A, TX-TE.A, U8.4 (VCCIO), U8.20 (VCC), U$28.5 (VOUT)
SW_USB+_TH: ADUM2.1 (VDD1), C9.1, C11.1, C13.1, C14.1, R38.2, R41.1, RX-TH.A, TX-TH.A, U3.4 (VCCIO), U3.20 (VCC), U$31.5 (VOUT)
TE_EN: R80.2, U13.49 ((T1)_PD6)
TH_EN: R30.2, U13.97 (PF0_(ADC0))
TX_BP: ADUM1402.12 (VIC), U13.3 ((TXD0)_PE1)
TX_BP_ISO: ADUM1402.5 (VOC), U2.5 (RXD)
TX_CAN: ADUM1.12 (VIC), U1.31 (PD1(TXD))
TX_CAN_ISO: ADUM1.5 (VOC), U6.5 (RXD)
TX_PMB1_ISO: U9.5 (RXD), U$8.P$5
TX_PMB2_ISO: U11.5 (RXD), U$9.P$5
TX_SA: ADUM3.12 (VIC), U$16.B4
TX_SA_1: SPARE2.1, U$16.A4
TX_SA_ISO: ADUM3.5 (VOC), U7.5 (RXD)
TX_TE: ADUM4.12 (VIC), U$11.B4
TX_TE_ISO: ADUM4.5 (VOC), U8.5 (RXD)
TX_TH: ADUM2.12 (VIC), U$45.L4
TX_TH_ISO: ADUM2.5 (VOC), U3.5 (RXD)
USB+_BP: FERRITE.1, U$30.U1 (UVCC)
USB+_CAN: FERRITE6.1, U$41.U1 (UVCC)
USB+_PMB1: FERRITE4.1, U$29.L1 (LVCC)
USB+_PMB2: FERRITE5.1, U$29.U1 (UVCC)
USB+_SA: FERRITE2.1, U$47.L1 (LVCC)
USB+_TE: FERRITE3.1, U$47.U1 (UVCC)
USB+_TH: FERRITE1.1, U$30.L1 (LVCC)
USB-_BP: ADUM1402.2 (GND1_2), ADUM1402.8 (GND1), C3.2, C5.2, C7.2, C8.2, SW_USB_BP.A, U2.7 (GND7), U2.18 (GND18), U2.21 (GND21), U2.25 (AGND), U2.26 (TEST), U$23.2 (GND), U$30.CHA3, U$30.CHA4, U$30.U4 (UGND)
USB-_CAN: ADUM1.2 (GND1_2), ADUM1.8 (GND1), C24.2, C57.2, C59.2, C60.2, SW_USB_CAN.A, U6.7 (GND7), U6.18 (GND18), U6.21 (GND21), U6.25 (AGND), U6.26 (TEST), U$41.CHA1, U$41.CHA2, U$41.CHA3, U$41.CHA4, U$41.U4 (UGND), U$53.2 (GND)
USB-_PMB1: C45.2, C46.2, SW_USB_PMB1.A, U9.7 (GND7), U9.18 (GND18), U9.21 (GND21), U9.25 (AGND), U9.26 (TEST), U$8.P$1, U$29.CHA1, U$29.CHA2, U$29.L4 (LGND), U$49.2 (GND)
USB-_PMB2: C51.2, C52.2, SW_USB_PMB2.A, U11.7 (GND7), U11.18 (GND18), U11.21 (GND21), U11.25 (AGND), U11.26 (TEST), U$9.P$1, U$29.CHA3, U$29.CHA4, U$29.U4 (UGND), U$51.2 (GND)
USB-_SA: ADUM3.2 (GND1_2), ADUM3.8 (GND1), C29.2, C31.2, C33.2, C34.2, SW_USB_SA1.A, U7.7 (GND7), U7.18 (GND18), U7.21 (GND21), U7.25 (AGND), U7.26 (TEST), U$44.2 (GND), U$47.CHA1, U$47.CHA2, U$47.L4 (LGND)
USB-_TE: ADUM4.2 (GND1_2), ADUM4.8 (GND1), C35.2, C37.2, C39.2, C40.2, SW_USB_TE.A, U8.7 (GND7), U8.18 (GND18), U8.21 (GND21), U8.25 (AGND), U8.26 (TEST), U$28.2 (GND), U$47.CHA3, U$47.CHA4, U$47.U4 (UGND)
USB-_TH: ADUM2.2 (GND1_2), ADUM2.8 (GND1), C9.2, C11.2, C13.2, C14.2, SW_USB_SA.A, U3.7 (GND7), U3.18 (GND18), U3.21 (GND21), U3.25 (AGND), U3.26 (TEST), U$30.CHA1, U$30.CHA2, U$30.L4 (LGND), U$31.2 (GND)
VREC: C54.P$2 (-), U5.12 (VREC), U5.16 (EN)
VREC2: C53.P$2 (-), U4.12 (VREC), U4.16 (EN)

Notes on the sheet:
telemetry board
thruster board
S&A board
to ethernet switch
to sonar
to nav housing
to acoustic
to kill switch
Soft-start
Daughter boards power control
Load balancer
Power connectors
backplane MCU
Isolated USB-UART converters
USB-UART converters
CAN-USB converter
Power over Ethernet injectors
CAN connectors
Current measurements
Voltage measurements
POEs power control
12V fan power
CAN-USB CONVERTER
VOLTAGE MEASUREMENT
CAN CONNECTORS
CURRENT MEASUREMENT
POE
LOAD BALANCER
SOFT START
POWER CONN
BACKPLANE MCU
USB-UART CONVERTER
ISOLATED USB-UART CONVERTER
Temperature sensor
EEPROM

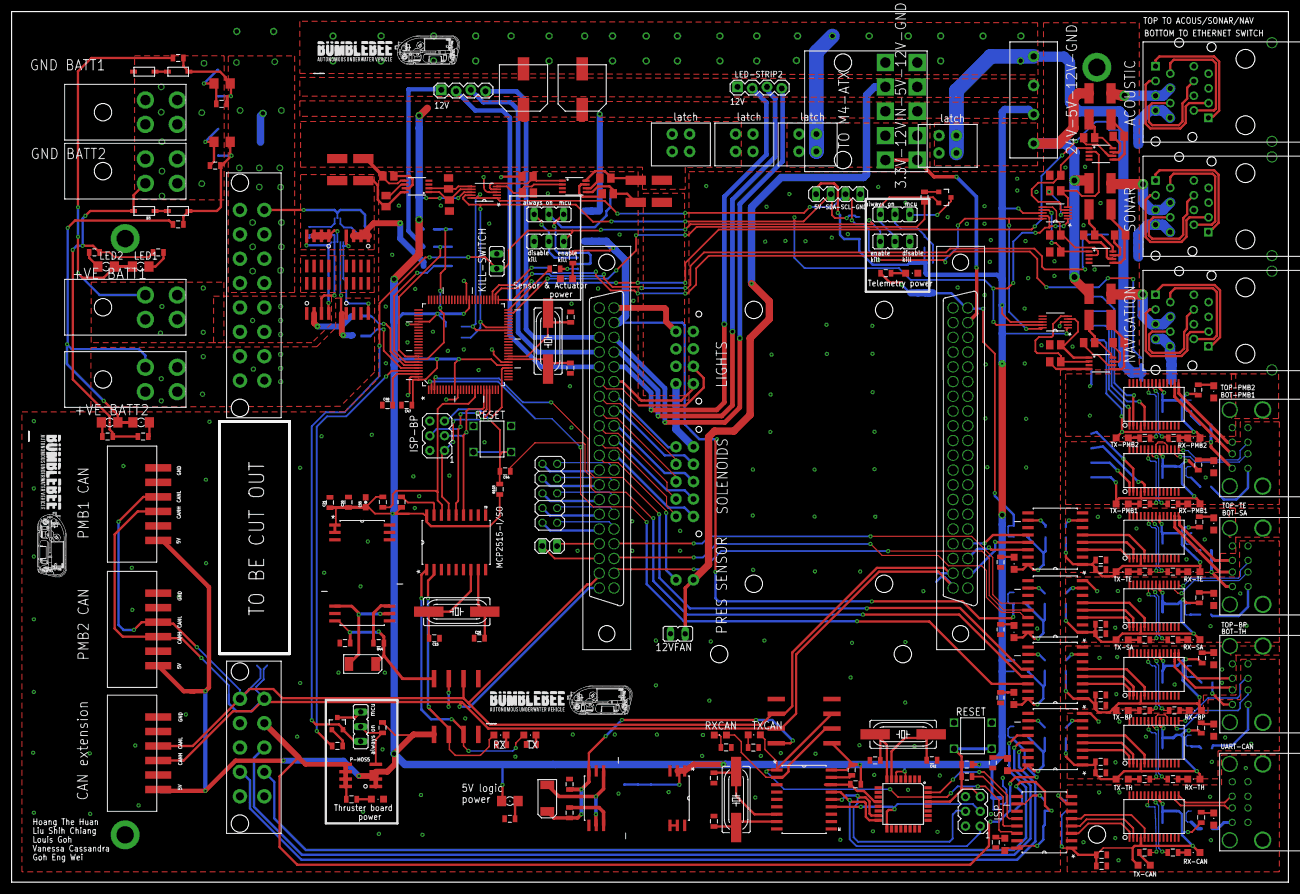
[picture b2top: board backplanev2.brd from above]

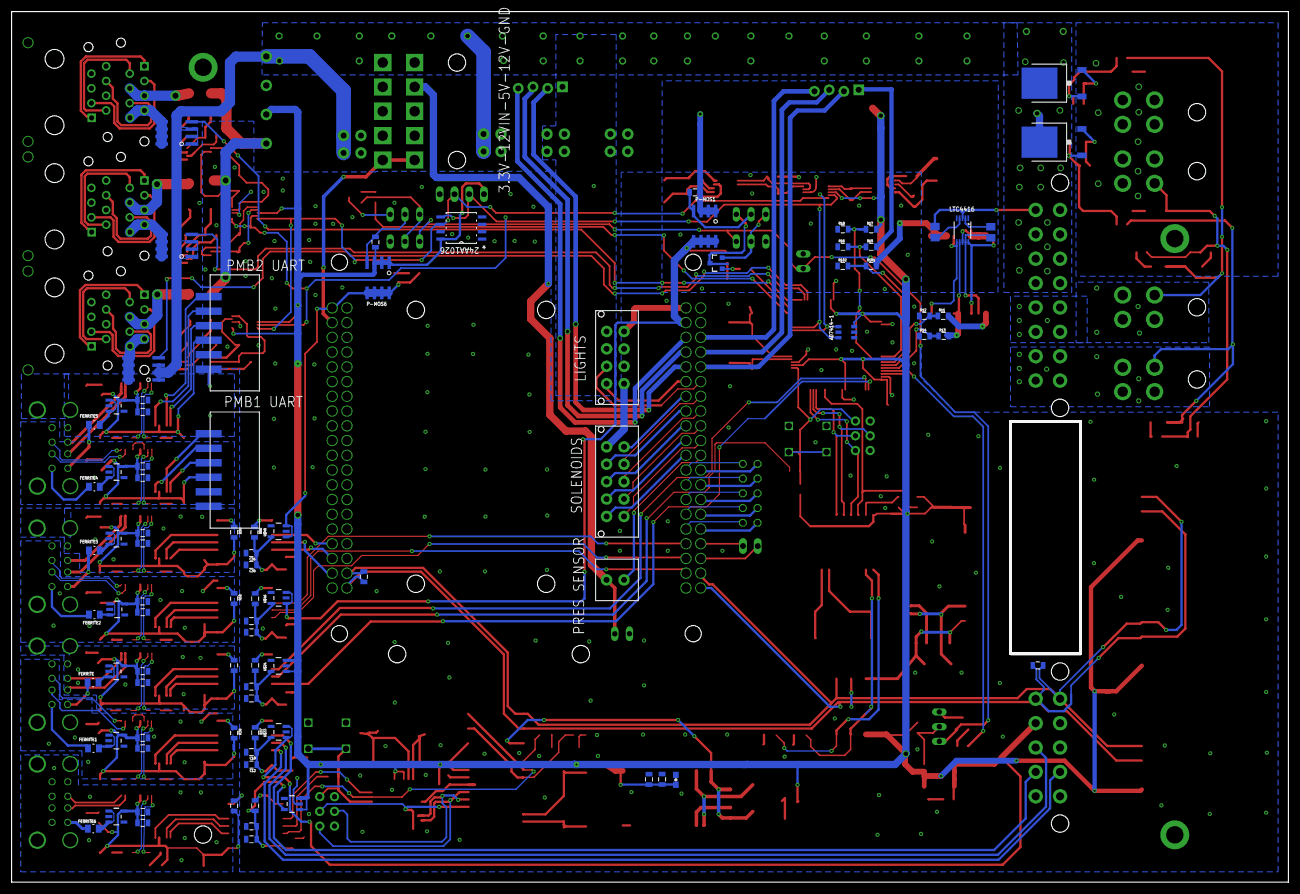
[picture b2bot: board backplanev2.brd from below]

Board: 2 copper layers, 220.0 x 150.0 mm, 327 parts (88 on the bottom side), 305 nets.

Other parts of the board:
U$66, U$67, U$68: BBAUV-LOGO-4

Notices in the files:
parts and their libraries:
SparkFun-Connectors: Licensing: Creative Commons ShareAlike 4.0 International - https://creativecommons.org/licenses/by-sa/4.0
SparkFun-Capacitors: Licensing: CC v3.0 Share-Alike You are welcome to use this library for commercial purposes.
